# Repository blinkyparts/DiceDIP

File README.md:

A simple soldering kit for an 6-sided dice. The random of the dice is depending on dicrect circuits.

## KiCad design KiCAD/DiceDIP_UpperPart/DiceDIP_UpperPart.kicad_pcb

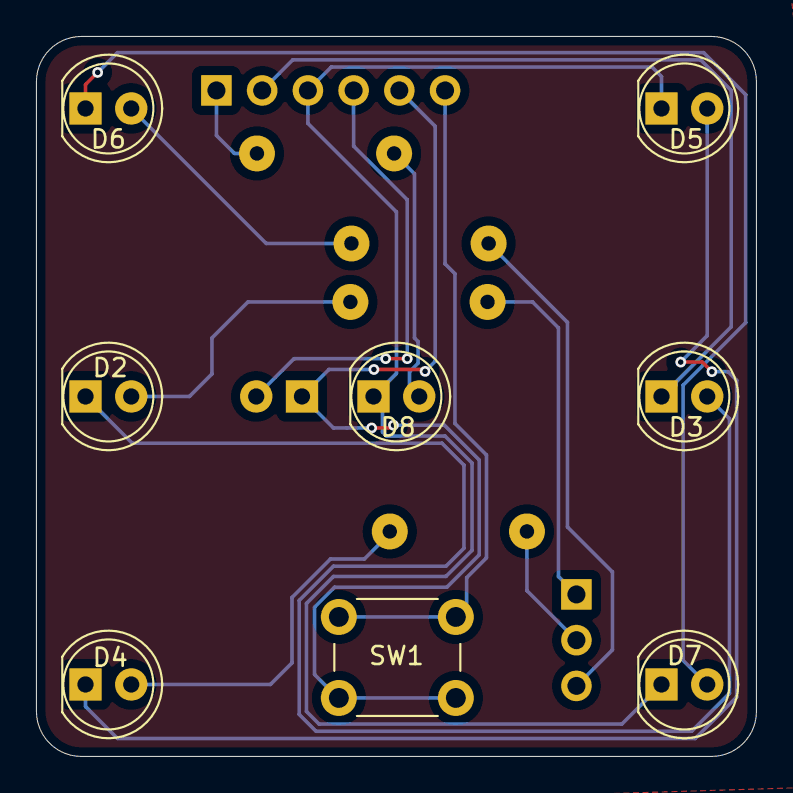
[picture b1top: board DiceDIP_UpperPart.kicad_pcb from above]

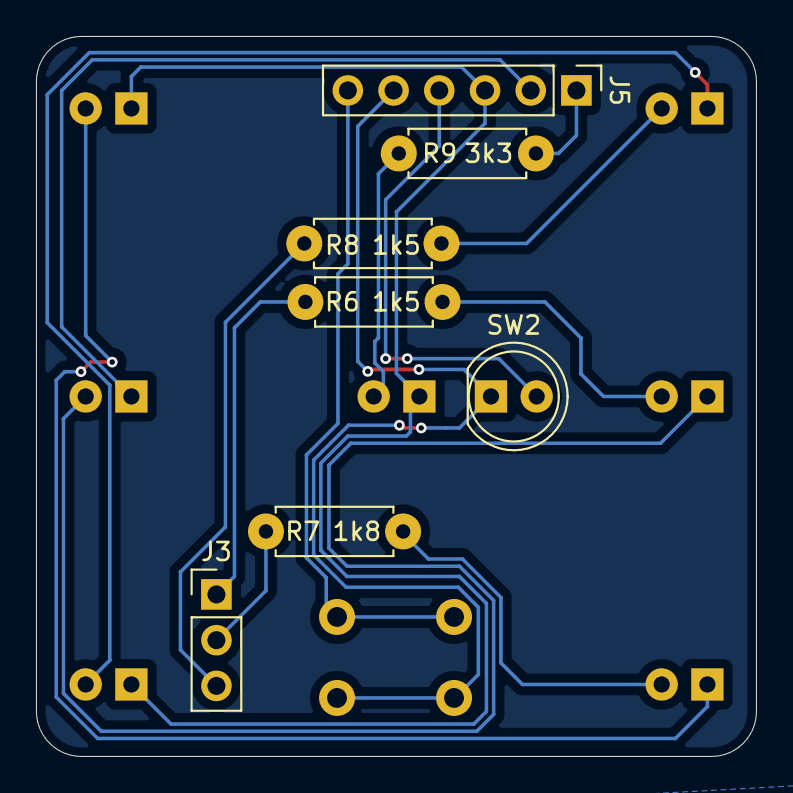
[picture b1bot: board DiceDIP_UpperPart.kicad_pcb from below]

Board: 2 copper layers, 40.0 x 40.0 mm, 18 parts (9 on the bottom side), 16 nets.

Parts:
D2, D3, D4, D5, D6, D7, D8: LED; LED_D5.0mm
J3: Conn_01x03; PinHeader_1x03_P2.54mm_Vertical
J5: Conn_01x06; PinHeader_1x06_P2.54mm_Vertical
R6, R8: 1k5; R_Axial_DIN0207_L6.3mm_D2.5mm_P7.62mm_Horizontal_handsolder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
R7: 1k8; R_Axial_DIN0207_L6.3mm_D2.5mm_P7.62mm_Horizontal_handsolder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
R9: 3k3; R_Axial_DIN0207_L6.3mm_D2.5mm_P7.62mm_Horizontal_handsolder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
SW1: SW_Push; SW_PUSH_6mm_H5mm
SW2: SW_Push; LED_D5.0mm
blinkyparts_logo_5mm: G***; logo_blinkyparts_5mm_F.Mask
ce-symbol_mask_3mm: G***; legislation_ce-icon_3mm_F.Mask
weee-symbol_mask_3mm: G***; legislation_weee-icon_3mm_F.Mask

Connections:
unnamed: D2.2 (A), R6.1
unnamed: D2.1 (K), D3.2 (A)
unnamed: D3.1 (K), J5.2
unnamed: D4.2 (A), R7.1
unnamed: D4.1 (K), D5.2 (A)
unnamed: D5.1 (K), D7.1 (K), D8.1 (K), J5.3
unnamed: D6.2 (A), R8.1
unnamed: D6.1 (K), D7.2 (A)
unnamed: D8.2 (A), R9.1
unnamed: J3.1, R6.2
unnamed: J3.2, R7.2
unnamed: J3.3, R8.2
unnamed: J5.1, R9.2
unnamed: J5.4, SW2.2
unnamed: J5.5, SW1.2, SW2.1
unnamed: J5.6, SW1.1

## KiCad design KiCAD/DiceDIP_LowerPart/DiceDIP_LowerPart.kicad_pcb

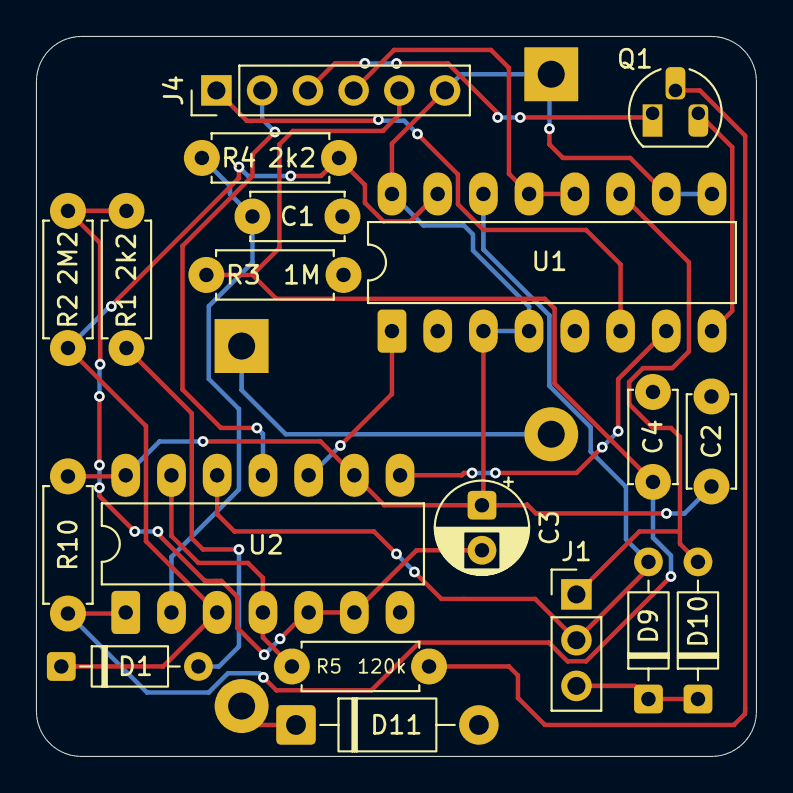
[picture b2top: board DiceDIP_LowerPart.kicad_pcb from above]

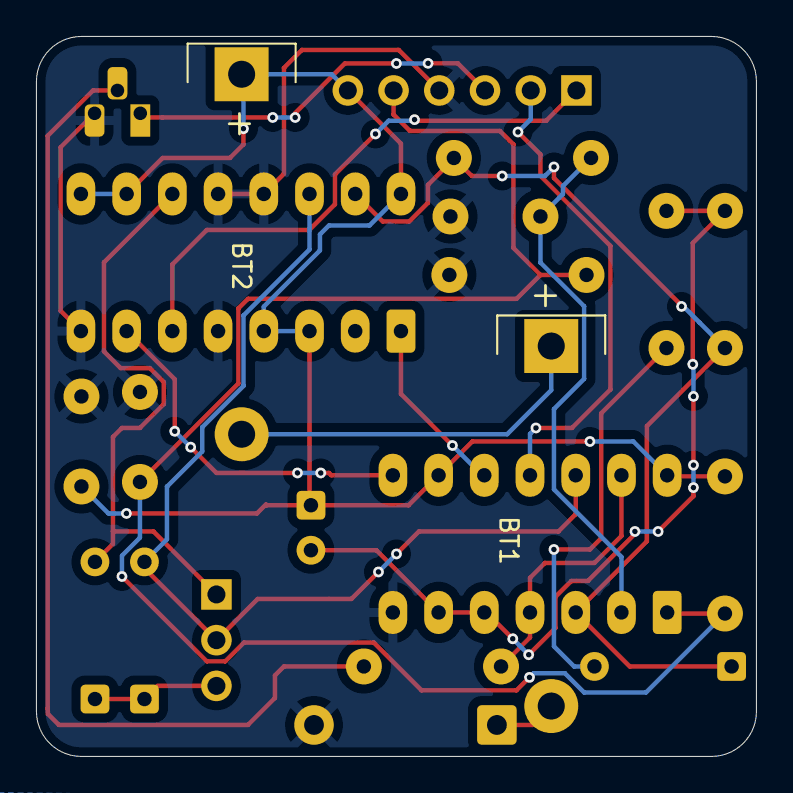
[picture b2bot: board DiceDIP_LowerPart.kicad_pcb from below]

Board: 2 copper layers, 40.0 x 40.0 mm, 24 parts (5 on the bottom side), 19 nets.

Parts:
BT1, BT2: Battery_Cell; BatteryHolder_CR2032_schwarz
C1, C2: 100nF; C_Disc_D5.0mm_W2.5mm_P5.00mm_handsoldering
C3: 47uF; CP_Radial_D5.0mm_P2.50mm
C4: C; C_Disc_D5.0mm_W2.5mm_P5.00mm_handsoldering
D1, D9, D10: BAW76; D_DO-35_SOD27_P7.62mm_Horizontal
D11: 1N4007; D_DO-41_SOD81_P10.16mm_Horizontal
J1: Conn_01x03; PinHeader_1x03_P2.54mm_Vertical
J4: Conn_01x06; PinHeader_1x06_P2.54mm_Vertical
Q1: BC547; TO-92_HandSolder
R1, R4: 2k2; R_Axial_DIN0207_L6.3mm_D2.5mm_P7.62mm_Horizontal_handsolder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
R2: 2M2; R_Axial_DIN0207_L6.3mm_D2.5mm_P7.62mm_Horizontal_handsolder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
R3: 1M; R_Axial_DIN0207_L6.3mm_D2.5mm_P7.62mm_Horizontal_handsolder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
R5: 120k; R_Axial_DIN0207_L6.3mm_D2.5mm_P7.62mm_Horizontal_handsolder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
R10: R; R_Axial_DIN0207_L6.3mm_D2.5mm_P7.62mm_Horizontal_handsolder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
U1: 4029; DIP-16_W7.62mm_LongPads
U2: 4093; DIP-14_W7.62mm_LongPads
blinkyparts_logo_5mm: G***; logo_blinkyparts_5mm_F.Mask
ce-symbol_mask_3mm: G***; legislation_ce-icon_3mm_F.Mask
weee-symbol_mask_3mm: G***; legislation_weee-icon_3mm_F.Mask

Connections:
unnamed: BT1.1 (+), BT2.2 (-)
unnamed: BT1.2 (-), D11.1 (K)
unnamed: C1.2, R4.1, U2.2
unnamed: C3.2, R1.2, R2.2, U2.5, U2.6
unnamed: D1.2 (A), R1.1
unnamed: D1.1 (K), R2.1, R4.2, U1.15 (CK), U2.3
unnamed: D9.2 (A), J1.2, U1.14 (Q3), U2.12
unnamed: D10.2 (A), J1.1, U1.11 (Q2)
unnamed: D9.1 (K), D10.1 (K), J1.3
unnamed: J4.1, U1.6 (Q1)
unnamed: J4.2, U2.11
unnamed: J4.3, Q1.1 (C)
unnamed: Q1.2 (B), R5.2
unnamed: R5.1, U2.4, U2.13
unnamed: U1.7 (Cout), U2.8
unnamed: U1.1 (PE), U2.10
SW_V1: C1.1, C2.1, C4.1, D11.2 (A), J4.4, Q1.3 (E), R3.1, U1.5 (Cin), U1.8 (VSS), U1.12 (J2), U1.13 (J3), U2.7 (Vss)
SW_V2: C4.2, J4.5, R3.2, R10.1, U2.1
VCC: BT2.1 (+), C2.2, C3.1, J4.6, R10.2, U1.3 (J4), U1.4 (J1), U1.9 (B/D), U1.10 (U/D), U1.16 (VDD), U2.9, U2.14 (Vdd)

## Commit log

2026-01-18 inital commit with original schematics by noby for v1.0
2026-01-18 inital readme
2026-01-18 first commit for v2.0 created with kicad and major layout changes
2026-01-19 routing upper side done
2026-01-25 minor changes
2026-01-25 added submodule and added legal stuff on lowerPart
2026-01-25 added name and version. Created gerber files for lowerPart
2026-01-25 added submodule for upperPart
2026-01-25 changed some silkscreen and updated gerber-files
2026-01-25 minor changes. Generated gerber files and zip
